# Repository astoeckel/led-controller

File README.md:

# LED Controller
## 4-channel high power LED buck converter constant current source

This repository contains the schematics and Gerber files for a four-channel high power LED constant current source with integrated 12-bit PWM dimmer. The circuit is built entirely from easily sourceable
through-hole components, and the two-layer PCB can be cheaply manufactured (expect about $15 for ten boards, excl. shipping, total cost of one board will be about $20, with high precision trimmer potentiometers and the ATmega88 AVR microcontroller being the most expensive parts).

## Specifications

* 9x10cm PCB dimension
* 7-25V DC input voltage (stabilised)
* Four independently controllable channels with 4096 PWM steps
* Max. 0.9A per channel, max. 3A total per board
* Daisy-chainable UART
* Automated ramping with configurable speed
* Lots of connections simplifying integration into other projects: small expansion header, power supply headers, fuse holder, DC jack, screwable connection terminals, ...

## About

This board is my first attempt at building a driver for high-power LEDs. LEDs must be driven with a constant current. A simple in-series resistor is often used for low-power LEDs, yet this is not really feasible for the high-power LEDs used in lighting applications due to temperature dependent voltage-current curves. A commonly used constant current source topology with high efficiency is the so called [buck converter](https://en.wikipedia.org/wiki/Buck_converter).

The low-side switched buck converter in this repository was designed from scratch. It does not rely on any specialized circuitry. Bare in mind that you probably shouldn't do this–integrated solutions exist that are much cheaper, smaller, and safer to use. However, they lack most of the learning experience.

The entire circuit was designed on a bread board first. Should you *really* intend to use it, I'd strongly recommend you make yourself familiar with the circuit by doing the same―though in that case you should go with a stripped down one-channel version.

Two of the PCBs are now at the heart of a wake-up light alarm-clock thingy with 36 high power LEDs (4 red, 4 green, 4 blue, 4 yellow, 20 white) in eight channels at 21.5V/300mA each and a total nominal light output of 3600 Lumen. Which is fairly bright. The boards have been tested for several hundred hours.

Schematic and board layout can be opened with [KiCad](http://kicad.org/). Important parts of the schematic are included as images in the next section (missing: the 3.3V power supply and lots of capacitors, as well as the AVR used for PWM). Final Gerber files for board production can be found in the `gerber` folder.

**⚠ Important:**
This is the first PCB I ever built and I am by no means an electrical engineer! This is just a hobby project. So all the information provided here should be taken with more than just a grain of salt. Use the documentation and schematics provided _at your own risk_. This circuit operates at fairly high currents and frequencies in the 100 kHz range. You are responsible for all shielding required to prevent any interference in the RF spectrum!

## How it works

In the following I'll go through most parts of the circuit diagram and explain them.

### Buck converter constant current source

The basic working principle of the buck converter is as depicted in the following
sketch:

*Case (a):*
When the n-channel MOSFET is conducting, a current flows through the load LED1; the current increases slowly over time due to the inductor L1. The current is monitored over the 1 Ohm shunt resistor pair R6/R7. Once the current reaches a certain threshold *ITh*, the MOSFET is switched off.

*Case (b):*
When the MOSFET is switched off, the magnetic field stored in the inductor maintains the current flow for a while. Once the measured current falls below the threshold current, the MOSFET can be safely switched on again.

Note that the IRLU 120N MOSFET used in the above schematic can be switched using logic-level voltages and does not require additional driver circuitry. You can safely build this circuit on a bread board with a (high-wattage) resistor as load and by manually switching the MOSFET from a 3.3V voltage source (or just using a switch instead of a MOSFET). Using an oscilloscope you should be able to measure something close to the above voltage trace sketches.

**Implementation details:** The shunt resistors R6/R7 must be 0.6W low tolerance resistors. There should be a low-ESR 100µF (or higher) electrolytic capacitor between VCC and GND close to the MOSFET to stabilise the power supply. Remember that the peak current through diode D2 will be the same as the current through your load, so use a fast-switching Schottky diode with corresponding current rating.

### Automating the switching process using a comperator

To build a constant current source we need to automate the switching process. Given a threshold reference voltage *UTh* the basic idea is to just use a comperator integrated circuit such as a LM339. If the measured voltage between IRAW1 in the above schematic and ground is above *UTh*, we switch the transistor on. And as soon as IRAW1 falls below *UTh*, we swtich the transistor off. Sounds simple enough.

A slight complication with this approach is that the comperator does not have infinite [common-mode rejection ratio](https://en.wikipedia.org/wiki/Common-mode_rejection_ratio). Let me unpack this. We are using an n-channel MOSFET as a low-side switch (in other words: the MOSFET switches the connection to ground). On the one hand, this makes controlling the MOSFET really easy, since we can just drive it from 3.3V logic circuitry, such as an AVR microcontroller. On the other hand, low-side switching requires to place the shunt resistor at the high side (close to VCC). Correspondingly, the reference voltage UTh and the sense voltage IRAW1 are both close to VCC (e.g. given a 1 Ohm resistor and a threshold current of 1A, *UTh* = VCC - 1V). A finite common mode rejection ratio means that comperators (or more general, operational amplifiers) do not work well in practice if both input voltages are shifted by a high common DC bias. We need some additional circuitry to shift the voltages towards the operating point of the comperator.

To solve this problem, I'm halving both UTh and IRAW1 using a voltage divider. The voltage divider for IRAW1-4 can be found in subfigure *(a)* of the above diagram. The reference voltage generation is depicted in subfigure *(b)*. Here, I'm using a -5V voltage regulator to generate a voltage of VCC - 5V. A 1k potentiometer with additional 4.7k resistor allows to generate a voltage in the range of about VCC to VCC - 0.8V (use a smaller value than 4.7k to increase the trimmer dynamic range and allow higher currents). This voltage is then divided by two using an additional (impedance matched) voltage divider stage.

Resistor voltage dividers are a crude solution. Their output voltage is highly susceptible to temperature variation and the actual current that is being drawn from the divider. Furthermore, dividing the voltage by two reduces the voltage difference between on- and off-state to a few hundred millivolts. Surprisingly, the solution works quite well in practice, as long as *ITh* is larger than a few tens of millivolts and VCC is constant (read: the driver cannot be used for standard LEDs with 20mA current, and you must use a stabilised DC power supply).

Subfigure *(c)* shows how the reference voltage REF1 and and measured voltage ISENSE1 are fed into the LM339 comperator. The comperator operates in an open-collector fashion, which allows to generate a logic level output signal between 0 and 3.3V using a pullup resistor. This signal is fed into a standard 74HCT04 inverting [Schmitt-Trigger](https://en.wikipedia.org/wiki/Schmitt_trigger), which generates a clean 3.3V binary TTL signal. I'm using a 74HCT08 AND gate to combine the output of the Schmitt trigger with an auxiliary logic signal. The auxiliary signal can be used to switch individual channels on and off and to dim LEDs using [PWM](https://en.wikipedia.org/wiki/Pulse-width_modulation).

### Dimming using pulse-width modulation (PWM)

To dim individual LED channels in 4096 steps I'm using an AVR microcontroller clocked at 8 MHz. Note that the AVR only provides high speed hardware PWM with 256 possible steps. Since brightness perception in biological systems (e.g. humans) is logarithmic, 256 are far to few steps to smoothly change brightness at low brightness values. E.g. the perceived brightness difference between levels "1" and "2" is rather extreme compared to the brightness difference between "254" and "255". To introduce more intermediate steps I'm using a technique called oversampling: the PWM is operated at a frequency 16 times higher than required for flicker-free operation, and the PWM value is slightly varied within each 16-cycle period. This variation depends on the lower 4-bit of the brightness value (marked with `l` in the following diagram).

            12-bit brightness value
            =======================
    
    msb                               lsb
     11 10  9  8  7  6  5  4  3  2  1  0
      h  h  h  h  h  h  h  h  l  l  l  l
     |----------------------|-----------|
          PWM base value     Oversampling

Given the current phase of a 16-cycle period and the `l` values, an additive offset in `{0, 1}` is looked up from the following table:
````c
uint16_t pwm_oversample_data[16] = {
    0b0000'0000'0000'0000, 0b1000'0000'0000'0000, 0b1000'0000'1000'0000,
    0b1000'1000'1000'0000, 0b1000'1000'1000'1000, 0b1001'1000'1000'1000,
    0b1001'1000'1001'1000, 0b1001'1000'1001'1001, 0b1001'1001'1001'1001,
    0b1101'1001'1001'1001, 0b1101'1001'1101'1001, 0b1101'1101'1101'1001,
    0b1101'1101'1101'1101, 0b1111'1101'1101'1101, 0b1111'1101'1111'1101,
    0b1111'1111'1111'1101,
};
````
Each entry corresponds to one of the possible 16 lower 4-bit values, and each bit in the sequence corresponds to an additive offset. The higher the lower 4-bit value, the longer the PWM value will be increased by one. This mechanism works really well in practice! See `src/avr/main.cpp` for more details.

### Controlling and flashing the AVR

The board contains a standard ISP connector for programming (I'm personally using a Raspberry Pi for programming AVR microcontrollers). Compile the software on Linux using the Makefile in the `src/avr` folder (requires an installed AVR `avr-gcc` toolchain). You can control the board with an UART connection using the `src/led_ctrl_host.cpp` program, for example using a cheap USB to UART cable. See `src/avr/bus.hpp` for a set of valid commands. Theoretically, up to 254 boards can be daisy-chained by connecting the TX-pin of one board to the RX-pin of the sibling board.

For example
```bash
./led_ctrl_host 0 2 0x3FFF
```
will set the brightness of the fourth channel (**3**FFF) of the first board (**0**) in the daisy chain to "FFF" (the maximum value),
```bash
./led_ctrl_host 0 1 0x0001
```
will set the ramp speed of of the first channel (**0**FFF) of the first board (**0**) in the daisy chain to the slowest possible value "1" (a value of "0" is off), and
```bash
./led_ctrl_host 0 0xFF 0x0000
```
will reset the first board in the daisy chain.

## How to build and test

Here is a short manual for building and testing the PCB. Be careful and use a current-limited bench power supply for testing.

1. Build the power supply circuitry containing the 3.3V and -5V linear regulators, as well as all low-profile capacitors. Apply power and make sure the correct voltages can be measured on the board (probe the schematic in *KiCad* to find the corresponding places on the PCB).
2. Add all the resistor arrays and the potentiometers. Make sure you can regulate the output voltage of the reference voltage generation stage in the interval between 0.5 * VCC and 0.5 * (VCC - 0.8V).
3. Add all remaining components except for the AVR. Instead, short circuit the AVR output pins (the free AND gate input pins) to 3.3V. Connect a test load (e.g. a 20 Ohm 20 Watt resistor) to the output terminals in series with a multimeter measuring the current. Reduce the current to a small value by adjusting the potentiometers. Replace the test load with your LEDs. Adjust the potentiometers until the desired current is reached (note that the output current gets smaller with increasing PCB temperature).
4. Add and program the ATmega88 (see above). Have fun.

## License

Note that this project consists of both hardware and to a smaller portion of software. Both parts are made available under different licenses.

### Hardware schematics

    Copyright Andreas Stöckel 2016, 2017.
    
    This documentation describes Open Hardware and is licensed under the
    CERN OHL v. 1.2. You may redistribute and modify this documentation under
    the terms of the CERN OHL v.1.2. (http://ohwr.org/cernohl). This
    documentation is distributed WITHOUT ANY EXPRESS OR IMPLIED WARRANTY,
    INCLUDING OF MERCHANTABILITY, SATISFACTORY QUALITY AND FITNESS FOR A
    PARTICULAR PURPOSE. Please see the CERN OHL v.1.2 for applicable conditions.

### Software (AVR firmware and host programs)

    This program is free software: you can redistribute it and/or modify
    it under the terms of the GNU General Public License as published by
    the Free Software Foundation, either version 3 of the License, or
    (at your option) any later version.
    
    This program is distributed in the hope that it will be useful,
    but WITHOUT ANY WARRANTY; without even the implied warranty of
    MERCHANTABILITY or FITNESS FOR A PARTICULAR PURPOSE.  See the
    GNU General Public License for more details.
    
    You should have received a copy of the GNU General Public License
    along with this program.  If not, see <http://www.gnu.org/licenses/>.

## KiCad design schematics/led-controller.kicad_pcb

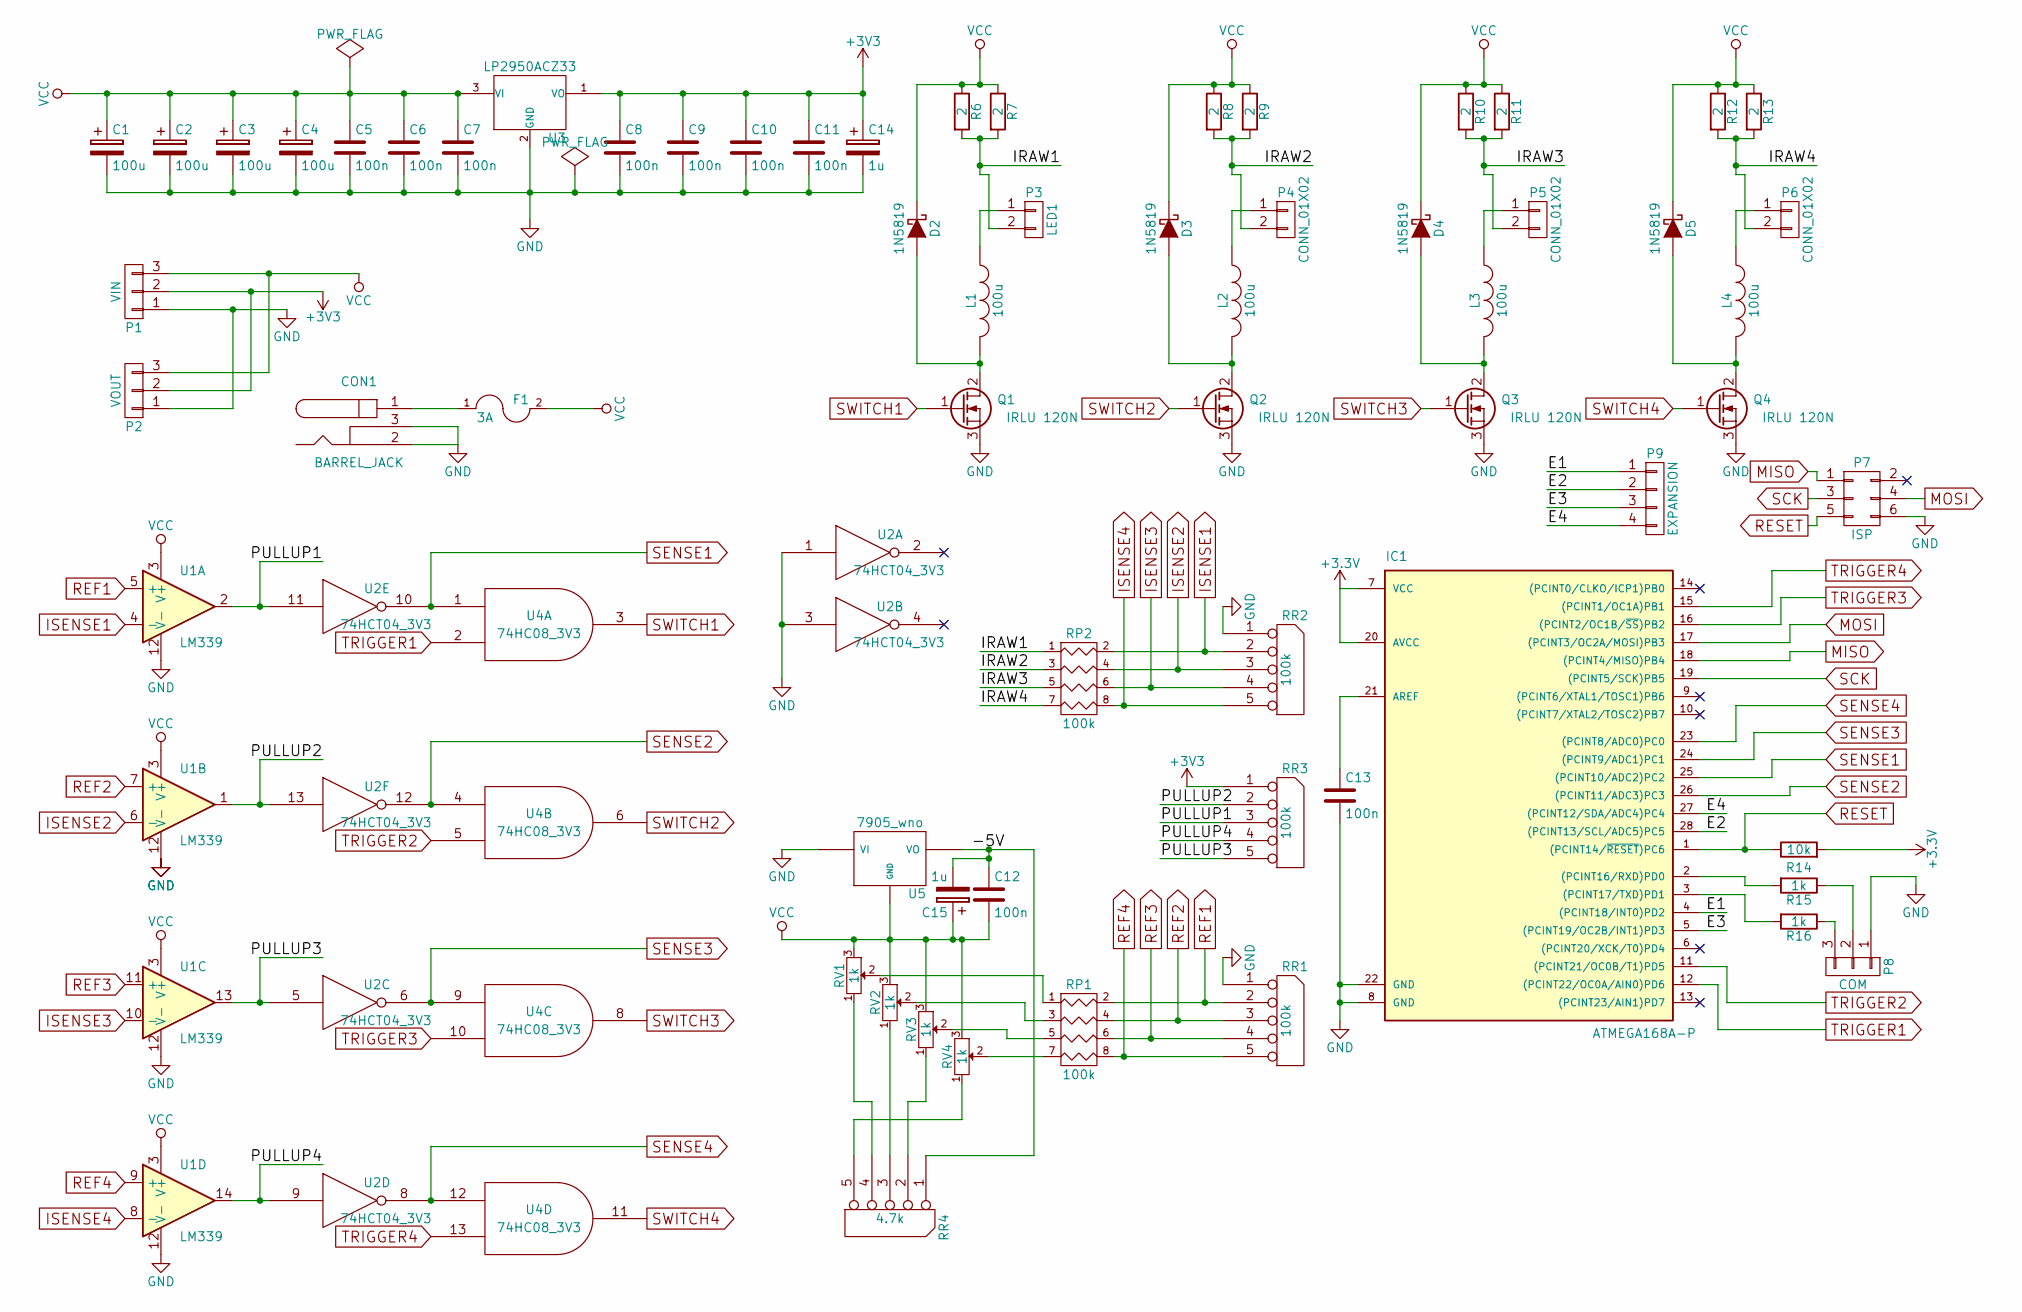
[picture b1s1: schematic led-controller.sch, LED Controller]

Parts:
C1, C2, C3, C4: 100u; C_Radial_D8_L11.5_P3.5
C5, C6, C7, C8, C9, C10, C11, C12, C13: 100n; C_Rect_L7_W2.5_P5
C14, C15: 1u; C_Radial_D5_L6_P2.5
CON1: BARREL_JACK
D2, D3, D4, D5: 1N5819; Diode_DO-35_SOD27_Horizontal_RM10
F1: 3A; Fuseholder5x20_horiz_open_lateral_Type-II
IC1: ATMEGA168A-P; DIP-28_W7.62mm
L1, L2, L3, L4: 100u; Neosid_Inductor_Sd8
P1: VIN; PINHEAD1-3
P2: VOUT; PINHEAD1-3
P3: LED1; bornier2
P4, P5, P6: CONN_01X02; bornier2
P7: ISP; Pin_Header_Straight_2x03
P8: COM; PINHEAD1-3
P9: EXPANSION; Pin_Header_Straight_1x04
Q1, Q2, Q3, Q4: IRLU 120N; TO-220_Neutral123_Vertical
R6, R7, R8, R9, R10, R11, R12, R13: 2; Resistor_Horizontal_RM10mm
R14: 10k; R1
R15, R16: 1k; R1
RP1, RP2: 100k; r-sil_8
RR1, RR2, RR3: 100k; r-sil_5
RR4: 4.7k; r-sil_5
RV1, RV2, RV3, RV4: 1k; Potentiometer_Trimmer-Suntan-TSR-3296
U1: LM339; DIP-14_W7.62mm
U2: 74HCT04_3V3; DIP-14_W7.62mm
U3: LP2950ACZ33; TO-92_Inline_Narrow_Oval
U4: 74HC08_3V3; DIP-14_W7.62mm
U5: 7905_wno; TO-92_Inline_Narrow_Oval

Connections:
/-5V: C12.1, C15.2, RR4.1 (COM), U5.3 (VO)
/E1: IC1.4 ((PCINT18/INT0)PD2), P9.1
/E2: IC1.28 ((PCINT13/SCL/ADC5)PC5), P9.2
/E3: IC1.5 ((PCINT19/OC2B/INT1)PD3), P9.3
/E4: IC1.27 ((PCINT12/SDA/ADC4)PC4), P9.4
/IRAW1: P3.2, R6.2, R7.2, RP2.1
/IRAW2: P4.2, R8.2, R9.2, RP2.3 (P2)
/IRAW3: P5.2, R10.2, R11.2, RP2.5 (P3)
/IRAW4: P6.2, R12.2, R13.2, RP2.7 (P4)
/PULLUP1: RR3.3, U1.2, U2.11
/PULLUP2: RR3.2, U1.1, U2.13
/PULLUP3: RR3.5, U1.13, U2.5
/PULLUP4: RR3.4, U1.14, U2.9
GND: C1.2, C2.2, C3.2, C4.2, C5.2, C6.2, C7.2, C8.2, C9.2, C10.2, C11.2, C13.2, C14.2, CON1.2, CON1.3, IC1.8 (GND), IC1.22 (GND), P1.1, P2.1, P7.6, P8.1, Q1.3 (S), Q2.3 (S), Q3.3 (S), Q4.3 (S), RR1.1 (COM), RR2.1 (COM), U1.12 (V-), U2.1, U2.3, U2.7 (GND), U3.2 (GND), U4.7 (GND), U5.2 (VI)
ISENSE1: RP2.2 (R1), RR2.2, U1.4 (-)
ISENSE2: RP2.4 (R2), RR2.3, U1.6 (-)
ISENSE3: RP2.6 (R3), RR2.4, U1.10 (-)
ISENSE4: RP2.8 (R4), RR2.5, U1.8 (-)
MISO: IC1.18 ((PCINT4/MISO)PB4), P7.1
MOSI: IC1.17 ((PCINT3/OC2A/MOSI)PB3), P7.4
unnamed: C13.1, IC1.21 (AREF)
unnamed: CON1.1, F1.1
unnamed: D2.2 (A), L1.2, Q1.2 (D)
unnamed: D3.2 (A), L2.2, Q2.2 (D)
unnamed: D4.2 (A), L3.2, Q3.2 (D)
unnamed: D5.2 (A), L4.2, Q4.2 (D)
unnamed: IC1.2 ((PCINT16/RXD)PD0), R15.2
unnamed: IC1.3 ((PCINT17/TXD)PD1), R16.2
unnamed: L1.1, P3.1
unnamed: L2.1, P4.1
unnamed: L3.1, P5.1
unnamed: L4.1, P6.1
unnamed: P8.2, R15.1
unnamed: P8.3, R16.1
unnamed: RP1.1, RV1.2
unnamed: RP1.3 (P2), RV2.2
unnamed: RP1.5 (P3), RV3.2
unnamed: RP1.7 (P4), RV4.2
unnamed: RR4.2, RV3.1 (3)
unnamed: RR4.3, RV2.1 (3)
unnamed: RR4.4, RV1.1 (3)
unnamed: RR4.5, RV4.1 (3)
REF1: RP1.2 (R1), RR1.2, U1.5 (+)
REF2: RP1.4 (R2), RR1.3, U1.7 (+)
REF3: RP1.6 (R3), RR1.4, U1.11 (+)
REF4: RP1.8 (R4), RR1.5, U1.9 (+)
RESET: IC1.1 ((PCINT14/~RESET~)PC6), P7.5, R14.1
SCK: IC1.19 ((PCINT5/SCK)PB5), P7.3
SENSE1: IC1.25 ((PCINT10/ADC2)PC2), U2.10, U4.1
SENSE2: IC1.26 ((PCINT11/ADC3)PC3), U2.12, U4.4
SENSE3: IC1.24 ((PCINT9/ADC1)PC1), U2.6, U4.9
SENSE4: IC1.23 ((PCINT8/ADC0)PC0), U2.8, U4.12
SWITCH1: Q1.1 (G), U4.3
SWITCH2: Q2.1 (G), U4.6
SWITCH3: Q3.1 (G), U4.8
SWITCH4: Q4.1 (G), U4.11
TRIGGER1: IC1.12 ((PCINT22/OC0A/AIN0)PD6), U4.2
TRIGGER2: IC1.11 ((PCINT21/OC0B/T1)PD5), U4.5
TRIGGER3: IC1.16 ((PCINT2/OC1B/~SS~)PB2), U4.10
TRIGGER4: IC1.15 ((PCINT1/OC1A)PB1), U4.13
VCC: C1.1, C2.1, C3.1, C4.1, C5.1, C6.1, C7.1, C12.2, C15.1, D2.1 (K), D3.1 (K), D4.1 (K), D5.1 (K), F1.2, P1.3, P2.3, R6.1, R7.1, R8.1, R9.1, R10.1, R11.1, R12.1, R13.1, RV1.3 (1), RV2.3 (1), RV3.3 (1), RV4.3 (1), U1.3 (V+), U3.3 (VI), U5.1 (GND)

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
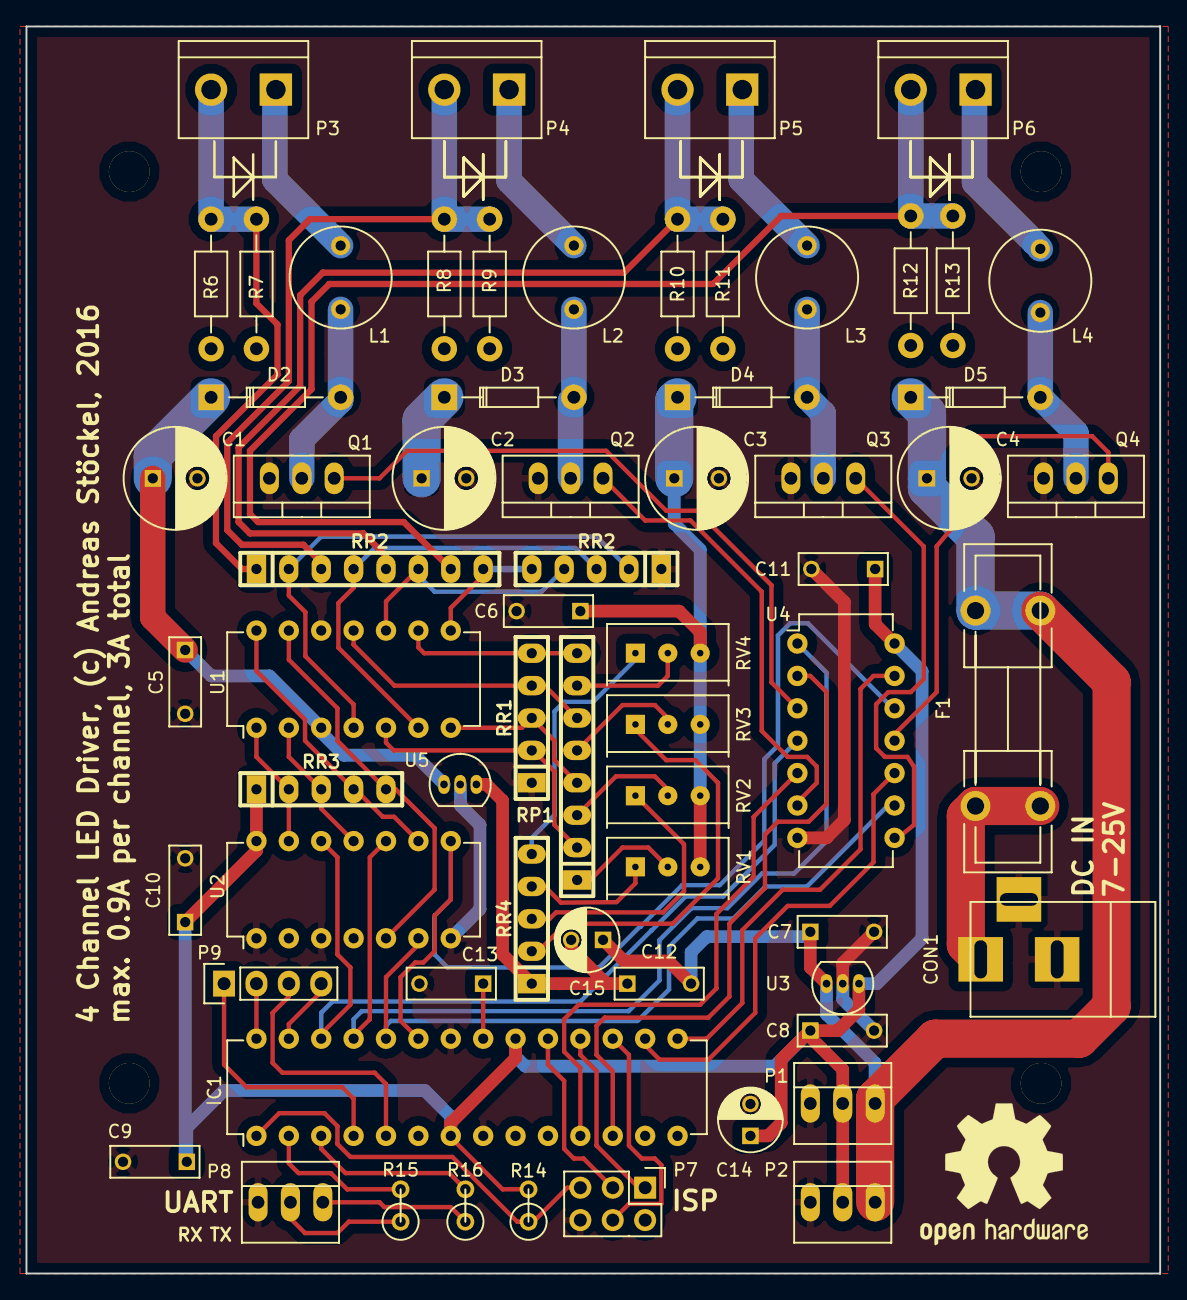
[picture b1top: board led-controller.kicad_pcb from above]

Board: 2 copper layers, 88.9 x 97.8 mm, 65 parts (0 on the bottom side), 62 nets.

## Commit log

2016-10-25 initial version
2016-10-28 add kicad schematic and first attempt at a pcb
2016-11-01 first checked version
2016-11-03 Improve PCB
    - Move mounting holes to 71.5mm distance, allows to attach the board to a
    80mm fan
    - Improve ground planes, remove one via
    - Prettify some tracks
2016-11-11 Board version 1.0 RC1
2016-11-27 Led Controller RC2
2016-11-27 RC3 -- Connected all pins to PWM outputs
2016-12-11 Fixed small issues found on the produced board
    - U3 was the wrong way round
    - Holes for diodes could have been a little bigger
2016-12-12 Implement actual 4-channel LED controller for the final board
    This version uses hardware PWM with 16-times oversampling for 12-bit resolution. Brightness values between 1 and 15 are currently not working correctly.
2017-06-25 Add documentation
2017-06-25 Add license header and remove stray test program
2017-06-25 Remove exported parts XML file
2017-06-25 Add forgotten library
2017-06-25 Remove original sPlan schematic
    I know Kicad.
2017-06-25 Add final Gerber files.
2017-06-25 Update README.
2017-06-25 Add annotated version of the photo
2017-06-25 Repair link
2017-06-25 More changes to README.md
2017-06-25 More improvements to README.md
2017-06-25 More proofreading.
2017-06-26 Yet more changes to README.md
2020-11-26 Random style improvements
2021-11-09 Update README.md
    https://forum.kicad.info/t/warning-avoid-all-links-to-kicad-pcb-org-use-kicad-org/31521
